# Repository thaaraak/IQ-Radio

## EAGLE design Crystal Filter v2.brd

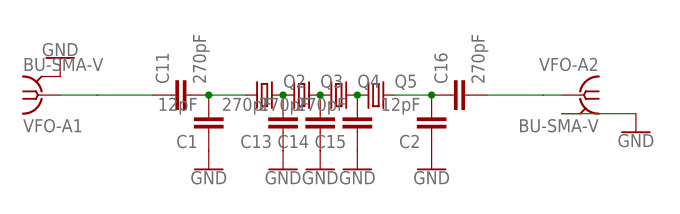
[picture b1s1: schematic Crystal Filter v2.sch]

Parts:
C1, C2: 12pF; C5B3.5
C11, C13, C14, C15, C16: 270pF; C5B3.5
Q2, Q3, Q4, Q5: CRYTALHC49S; HC49/S
VFO-A1, VFO-A2: BU-SMA-V

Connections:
GND: C1.1, C2.1, C13.1, C14.1, C15.1, VFO-A1.2, VFO-A1.3 (2), VFO-A1.4 (2), VFO-A1.5 (2), VFO-A2.2, VFO-A2.3 (2), VFO-A2.4 (2), VFO-A2.5 (2)
unnamed: C1.2, C11.2, Q2.1
unnamed: C16.2, VFO-A2.1
unnamed: C11.1, VFO-A1.1
unnamed: C2.2, C16.1, Q5.2
unnamed: C13.2, Q2.2, Q3.1
unnamed: C14.2, Q3.2, Q4.1
unnamed: C15.2, Q4.2, Q5.1

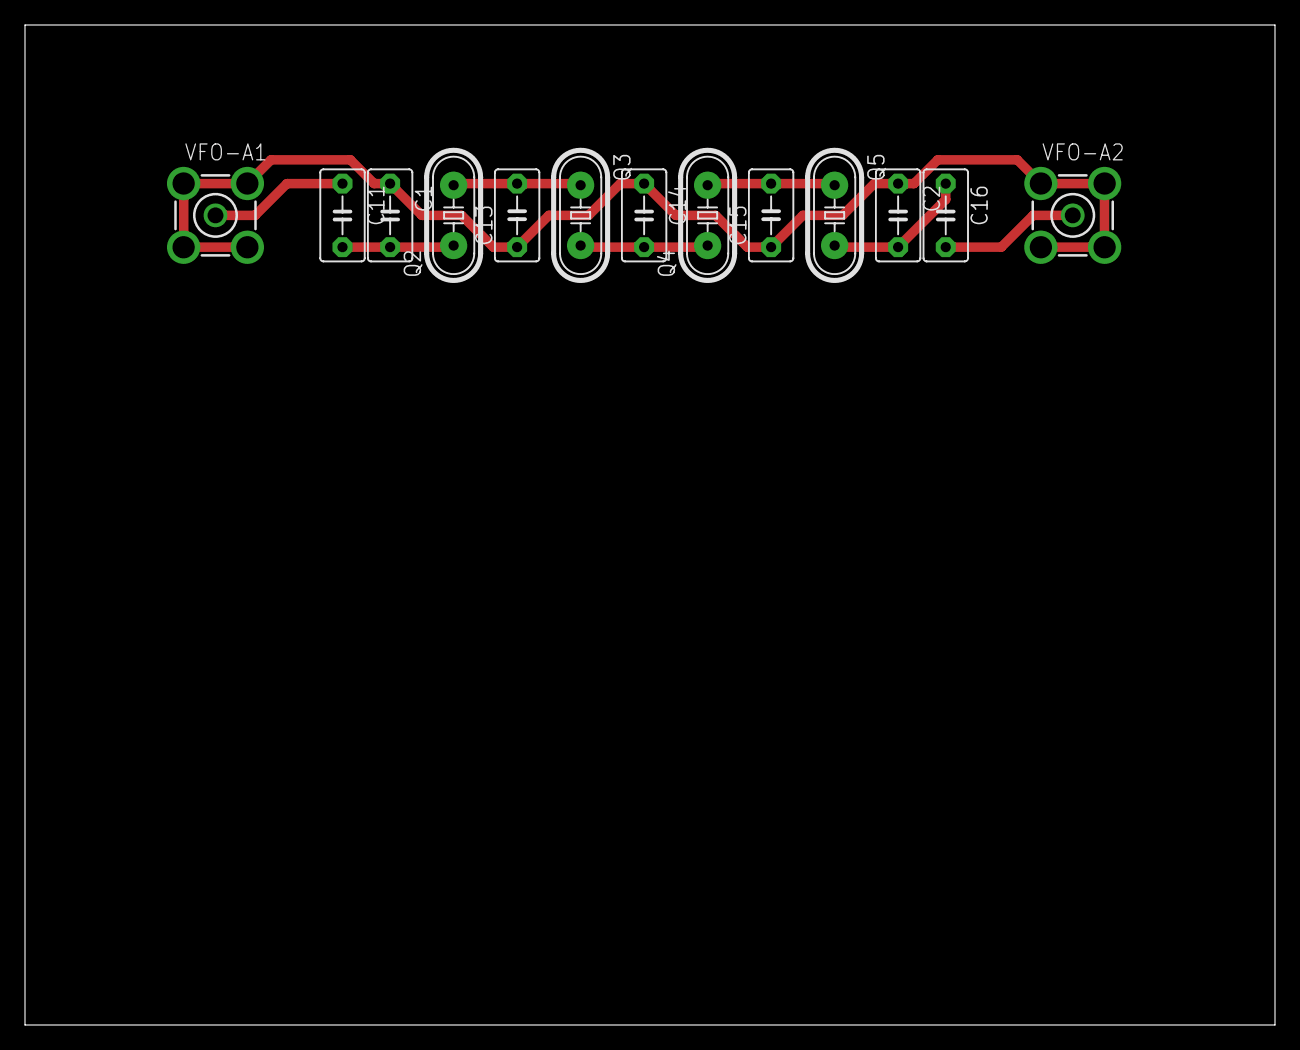
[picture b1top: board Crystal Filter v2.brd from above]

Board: 2 copper layers, 100.0 x 80.0 mm, 13 parts (0 on the bottom side), 8 nets.

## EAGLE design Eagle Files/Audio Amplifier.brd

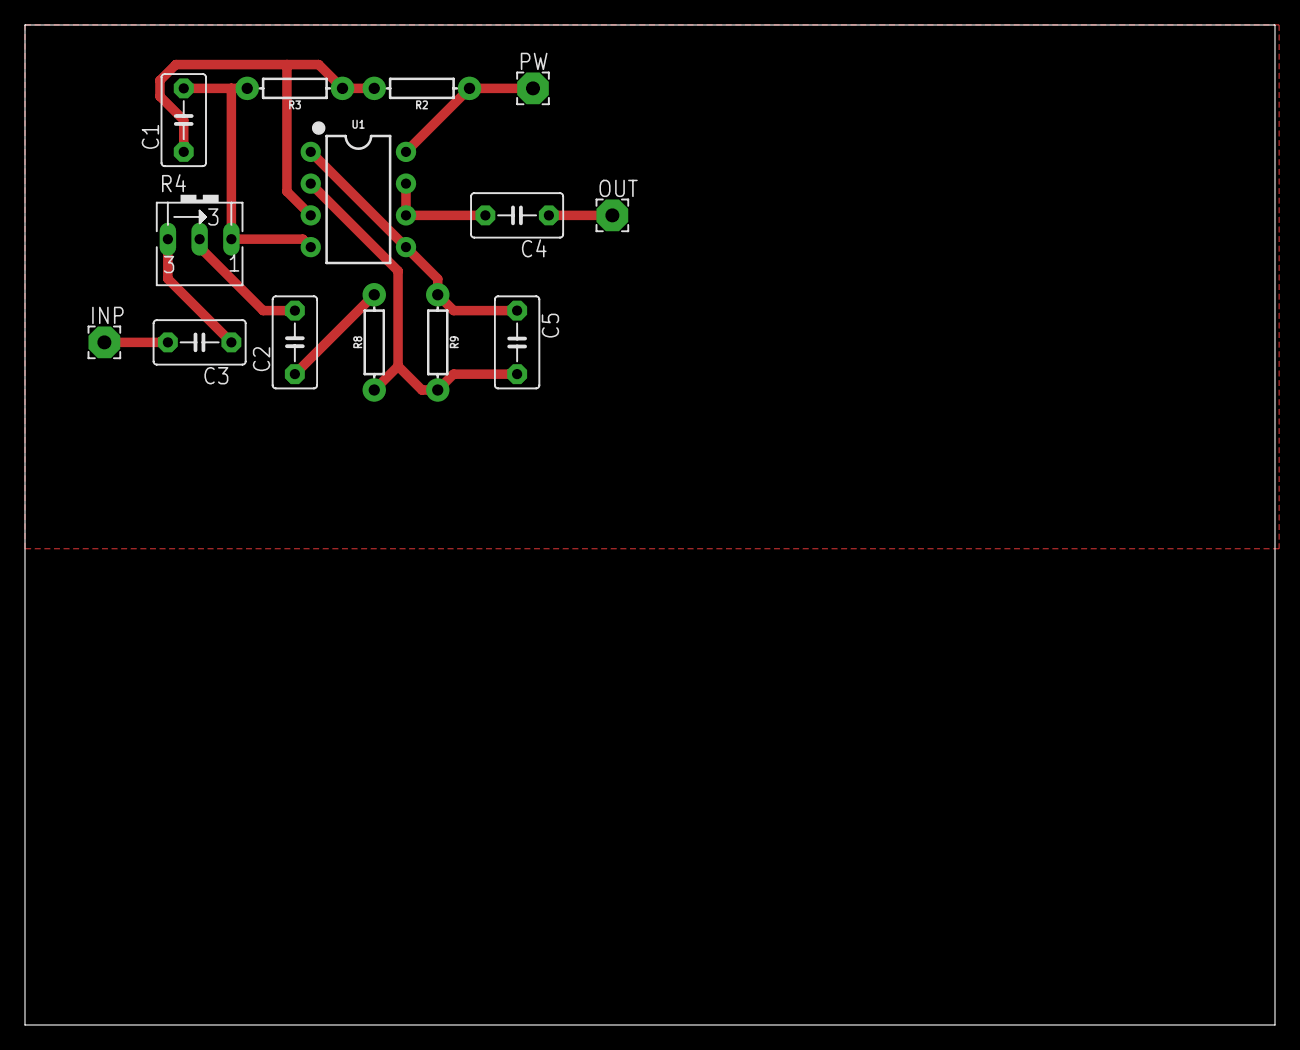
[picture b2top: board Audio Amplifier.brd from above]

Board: 2 copper layers, 100.0 x 80.0 mm, 14 parts (0 on the bottom side), 11 nets.

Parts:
C1, C4: 10uF; C5B3.5
C2, C3: 1uF; C5B3.5
C5: 1nF; C5B3.5
INP: 2,54/1,1
OUT: 2,54/1,1
PW: 2,54/1,1
R2, R3: 10k; AXIAL-0.3
R4: 5k; B25V
R8: 1k; AXIAL-0.3
R9: 120k; AXIAL-0.3
U1: LM358; DIP08

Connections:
GND: C1.2, R3.P$2, R4.A, U1.4
unnamed: C1.1, R2.P$2, R3.P$1, U1.3
unnamed: C2.1, R8.P$2
unnamed: C4.2, U1.6, U1.7
unnamed: C2.2, R4.S
unnamed: C3.1, R4.E
unnamed: C3.2, INP.1
unnamed: C5.2, R8.P$1, R9.P$2, U1.2
unnamed: C4.1, OUT.1
unnamed: C5.1, R9.P$1, U1.1, U1.5
VCC: PW.1, R2.P$1, U1.8

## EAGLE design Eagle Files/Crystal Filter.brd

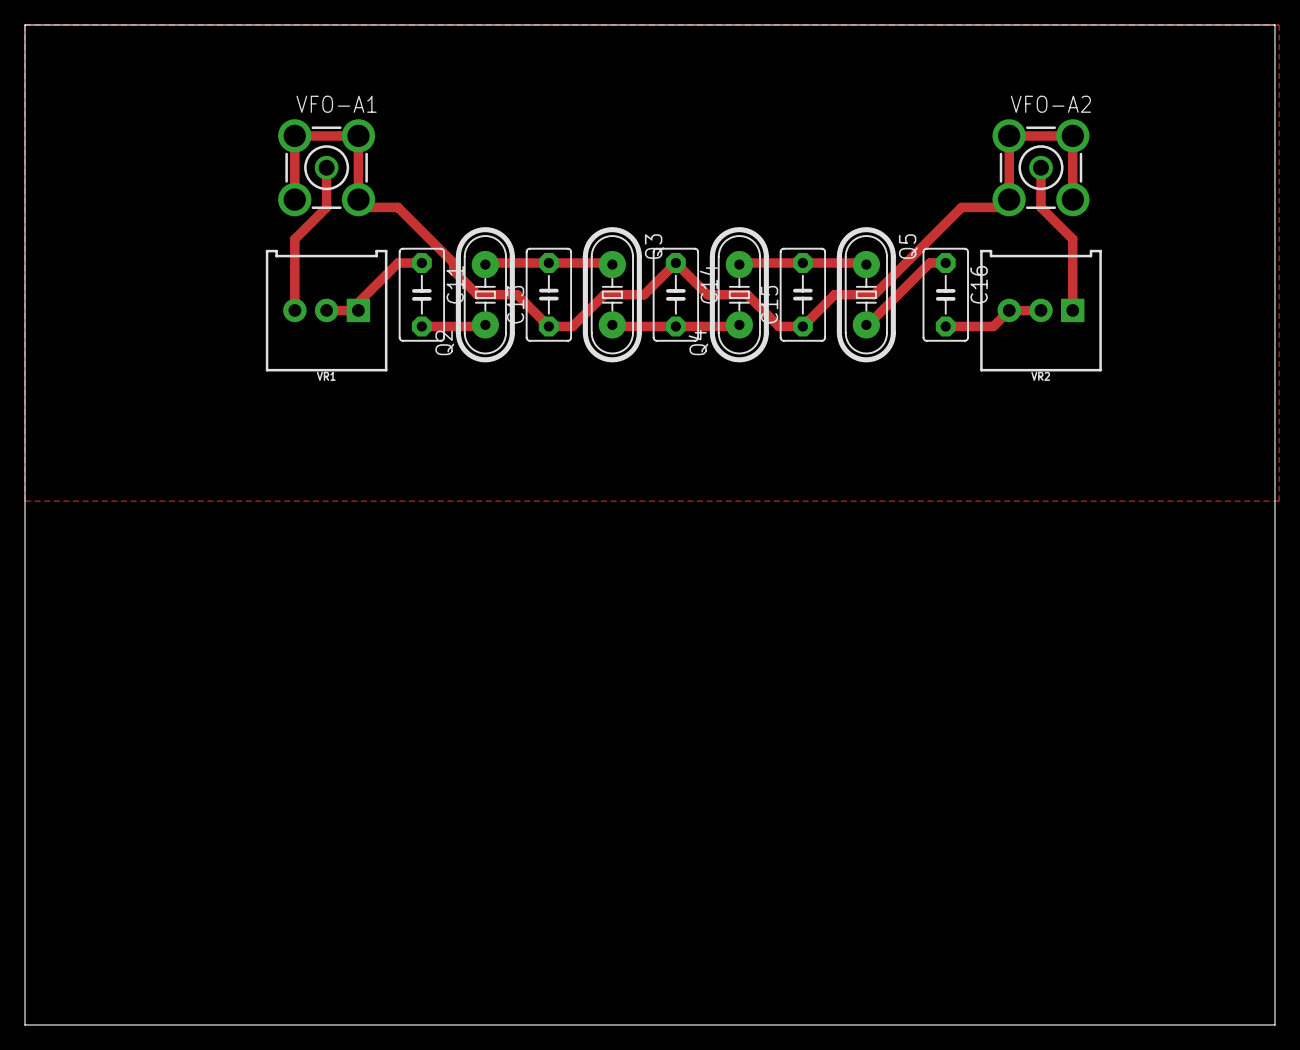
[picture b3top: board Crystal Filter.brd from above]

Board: 2 copper layers, 100.0 x 80.0 mm, 13 parts (0 on the bottom side), 10 nets.

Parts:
C11, C13, C14, C15, C16: 270pF; C5B3.5
Q2, Q3, Q4, Q5: HC49/S
VFO-A1, VFO-A2: BU-SMA-V
VR1, VR2: 500; TRIMPOT-PTH-3386U

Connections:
GND: C13.1, C14.1, C15.1, VFO-A1.2, VFO-A1.3, VFO-A1.4, VFO-A1.5, VFO-A2.2, VFO-A2.3, VFO-A2.4, VFO-A2.5
unnamed: C11.1, VR1.1, VR1.2
unnamed: C16.2, VR2.2, VR2.3
unnamed: VFO-A2.1, VR2.1
unnamed: VFO-A1.1, VR1.3
unnamed: C16.1, Q5.2
unnamed: C11.2, Q2.1
unnamed: C13.2, Q2.2, Q3.1
unnamed: C14.2, Q3.2, Q4.1
unnamed: C15.2, Q4.2, Q5.1

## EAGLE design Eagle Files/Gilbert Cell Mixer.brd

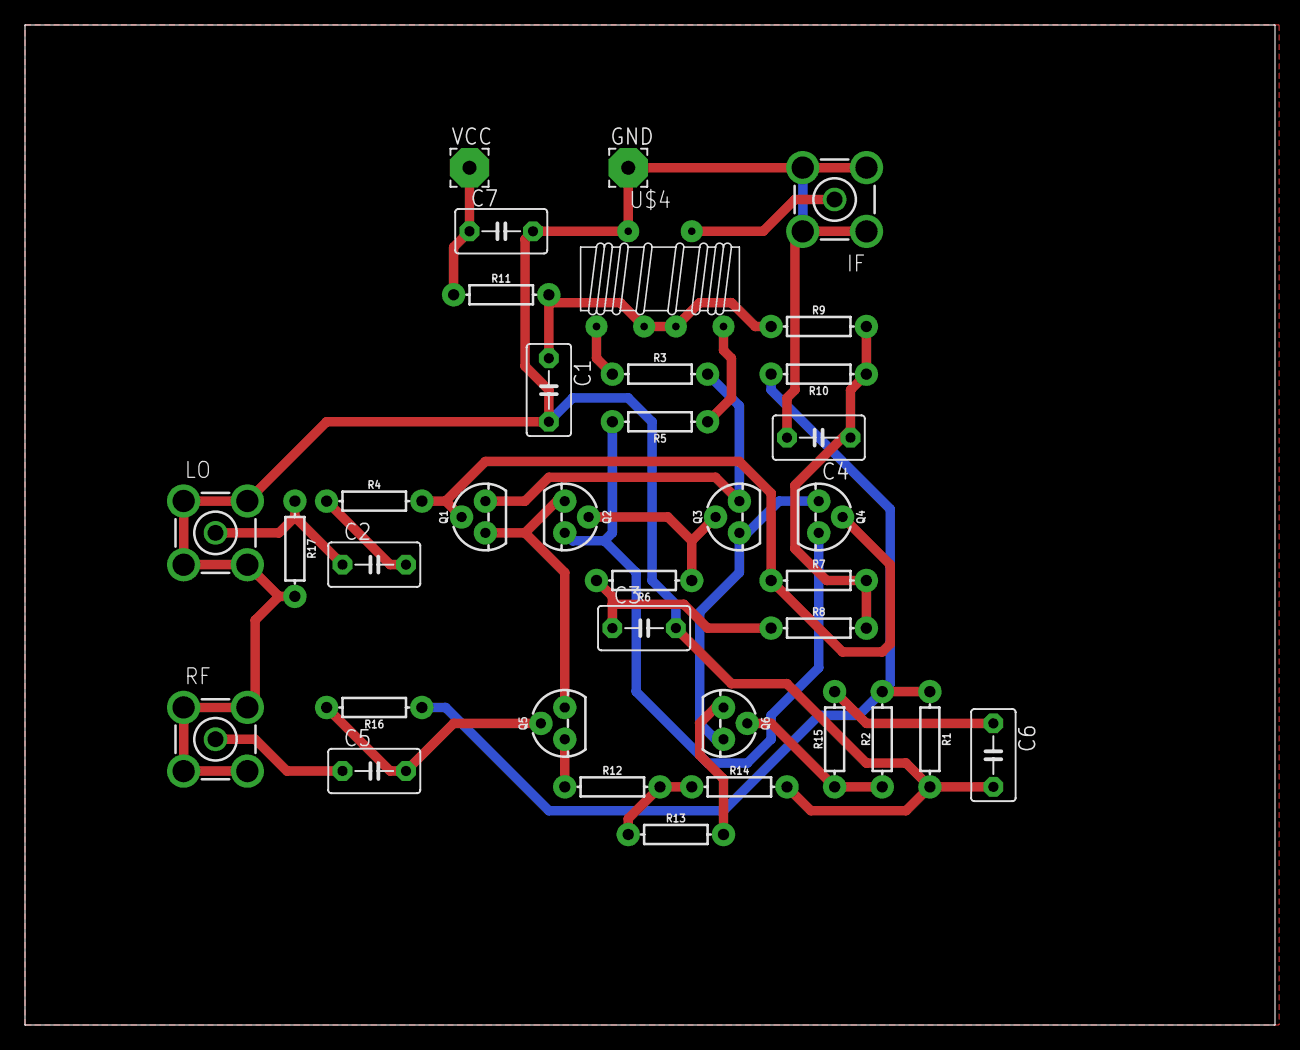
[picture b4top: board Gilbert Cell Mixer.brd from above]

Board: 2 copper layers, 100.0 x 80.0 mm, 36 parts (0 on the bottom side), 24 nets.

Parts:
C1, C2, C3, C4, C5, C6: .1uF; C5B3.5
C7: 100uF; C5B3.5
GND: 3,17/1,1
IF: BU-SMA-V
LO: BU-SMA-V
Q1, Q2, Q3, Q4, Q5, Q6: TO-92
R1: 2k; AXIAL-0.3
R2, R7, R8, R16: 2.2k; AXIAL-0.3
R3, R4, R5, R15: 36; AXIAL-0.3
R6: 10; AXIAL-0.3
R9: 4.7k; AXIAL-0.3
R10: 3k; AXIAL-0.3
R11: 100; AXIAL-0.3
R12, R13: 22; AXIAL-0.3
R14: 300; AXIAL-0.3
R17: 51; AXIAL-0.3
RF: BU-SMA-V
U$4: T50_SPLITTER
VCC: 3,17/1,1

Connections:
GND: C1.2, C3.2, C4.2, C6.2, C7.2, GND.1, IF.2, IF.3, IF.4, IF.5, LO.2, LO.3, LO.4, LO.5, R1.P$2, R14.P$2, R17.P$2, RF.2, RF.3, RF.4, RF.5, U$4.C1A
unnamed: Q1.1, Q2.1, Q5.3
unnamed: Q1.2, Q4.2, R4.P$2, R7.P$1
unnamed: R1.P$1, R2.P$2, R10.P$2, R16.P$1
unnamed: C1.1, R9.P$1, R11.P$2, U$4.C2A, U$4.C3A
unnamed: IF.1, U$4.C1B
unnamed: Q3.1, Q4.1, Q6.3
unnamed: Q1.3, Q3.3, R3.P$2
unnamed: C2.1, LO.1, R17.P$1
unnamed: C3.1, R6.P$2, R8.P$1
unnamed: Q2.3, Q4.3, R5.P$2
unnamed: C6.1, R15.P$2
unnamed: Q6.2, R2.P$1, R15.P$1
unnamed: Q2.2, Q3.2, R6.P$1
unnamed: C4.1, R7.P$2, R8.P$2, R9.P$2, R10.P$1
unnamed: R3.P$1, U$4.C2B
unnamed: R5.P$1, U$4.C3B
unnamed: C2.2, R4.P$1
unnamed: Q5.1, R12.P$1
unnamed: R12.P$2, R13.P$1, R14.P$1
unnamed: Q6.1, R13.P$2
unnamed: C5.1, RF.1
unnamed: C5.2, Q5.2, R16.P$2
VCC: C7.1, R11.P$1, VCC.1

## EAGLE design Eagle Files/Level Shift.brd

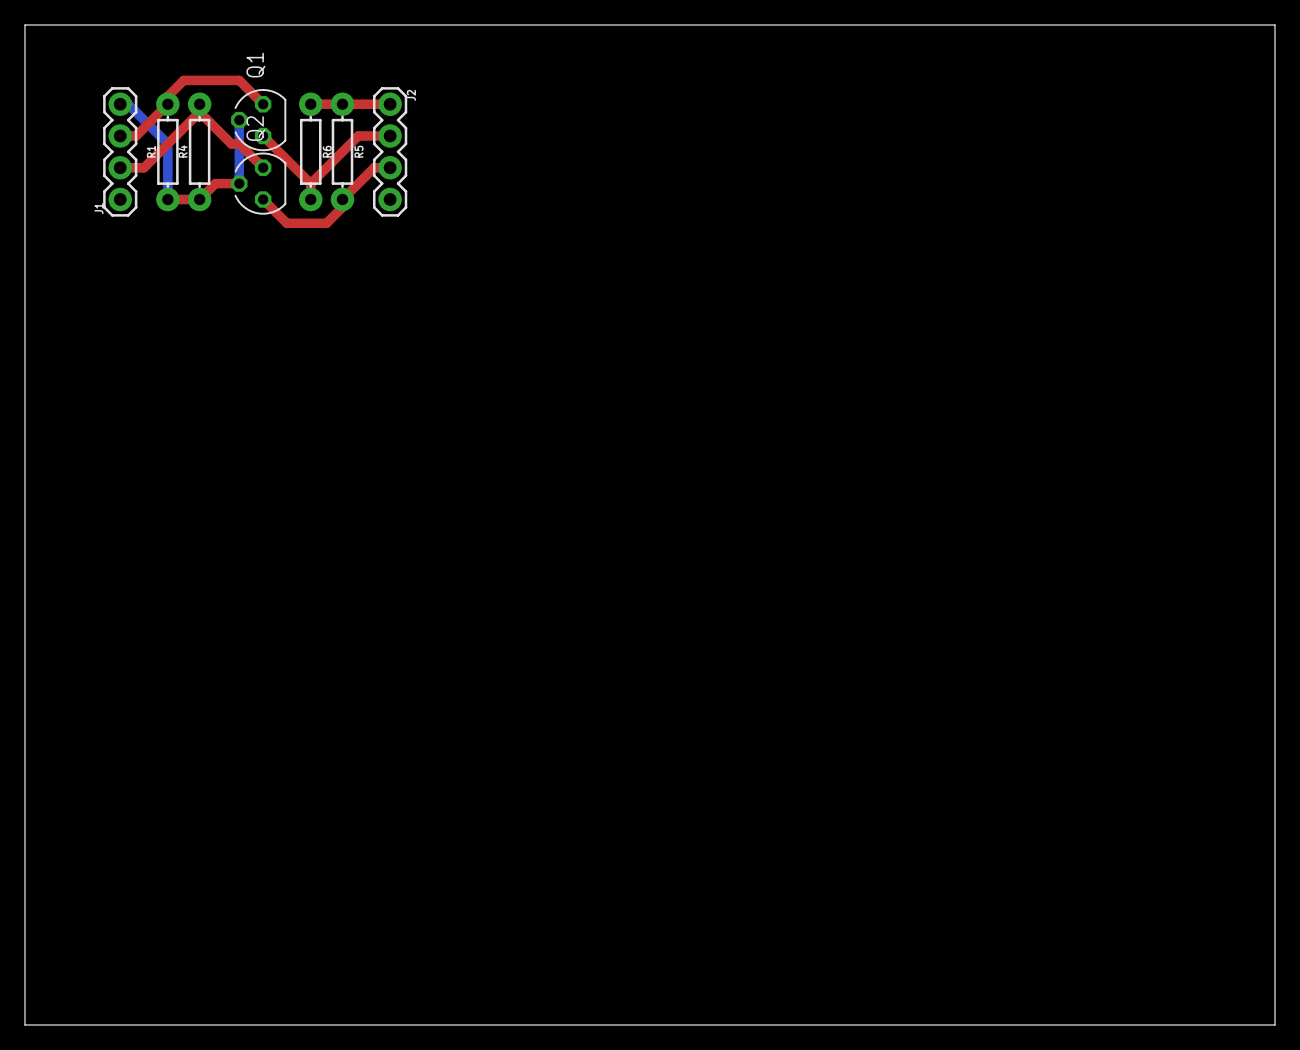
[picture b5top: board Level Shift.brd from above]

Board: 2 copper layers, 100.0 x 80.0 mm, 8 parts (0 on the bottom side), 6 nets.

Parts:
J1, J2: 1X04
Q1, Q2: BS170; SOT54E
R1, R4, R5, R6: 1k; AXIAL-0.3

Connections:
3V: J1.4, Q1.G, Q2.G, R1.P$1, R4.P$1
5V: J2.1, R5.P$1, R6.P$1
unnamed: J1.3, Q1.S, R1.P$2
unnamed: J2.2, Q1.D, R6.P$2
unnamed: J1.2, Q2.S, R4.P$2
unnamed: J2.3, Q2.D, R5.P$2

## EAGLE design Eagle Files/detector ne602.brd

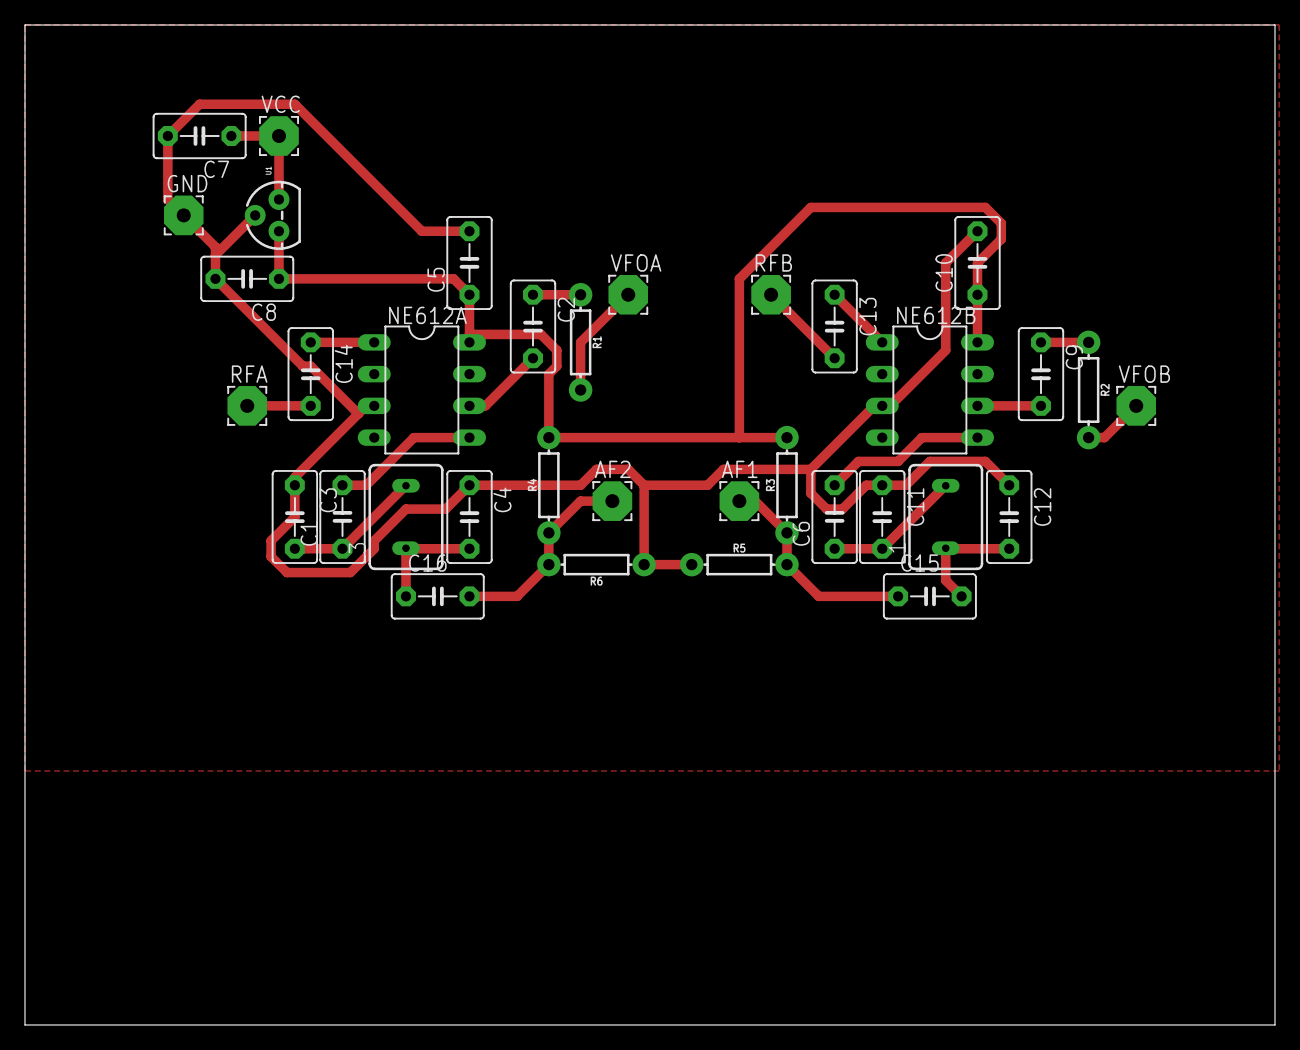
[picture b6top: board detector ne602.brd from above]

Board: 2 copper layers, 100.0 x 80.0 mm, 35 parts (0 on the bottom side), 21 nets.

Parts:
AF1, AF2: 3,17/1,1
C1, C6: 10uF; C5B3.5
C2, C3, C4, C9, C11, C12, C13, C14, C15, C16: 100nF; C5B3.5
C5, C10: .047uF; C5B3.5
C7: 100uF; C5B3.5
C8: 22uf; C5B3.5
GND: 3,17/1,1
L1, L3: 1mH; BS75
NE612A, NE612B: DIL08
R1, R2, R5, R6: 4.7k; AXIAL-0.3
R3, R4: 7.5; AXIAL-0.3
RFA: 3,17/1,1
RFB: 3,17/1,1
U1: TO-92
VCC: 3,17/1,1
VFOA: 3,17/1,1
VFOB: 3,17/1,1

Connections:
8V: C5.1, C8.1, C10.1, NE612A.8, NE612B.8, R3.P$2, R4.P$2, U1.1
GND: C3.1, C4.1, C5.2, C7.2, C8.2, C10.2, C11.1, C12.1, GND.1, NE612A.3, NE612B.3, R5.P$1, R6.P$1, U1.2
unnamed: C1.2, NE612A.5
unnamed: C2.2, NE612A.6
unnamed: C1.1, C3.2, L3.2
unnamed: C4.2, C16.1, L3.1
unnamed: C2.1, R1.P$1
unnamed: R1.P$2, VFOA.1
unnamed: C13.1, NE612B.1
unnamed: C6.2, NE612B.5
unnamed: C9.2, NE612B.6
unnamed: C6.1, C11.2, L1.2
unnamed: C12.2, C15.2, L1.1
unnamed: C9.1, R2.P$1
unnamed: R2.P$2, VFOB.1
unnamed: C14.1, NE612A.1
unnamed: C13.2, RFB.1
unnamed: C14.2, RFA.1
unnamed: AF1.1, C15.1, R3.P$1, R5.P$2
unnamed: AF2.1, C16.2, R4.P$1, R6.P$2
VCC: C7.1, U1.3, VCC.1

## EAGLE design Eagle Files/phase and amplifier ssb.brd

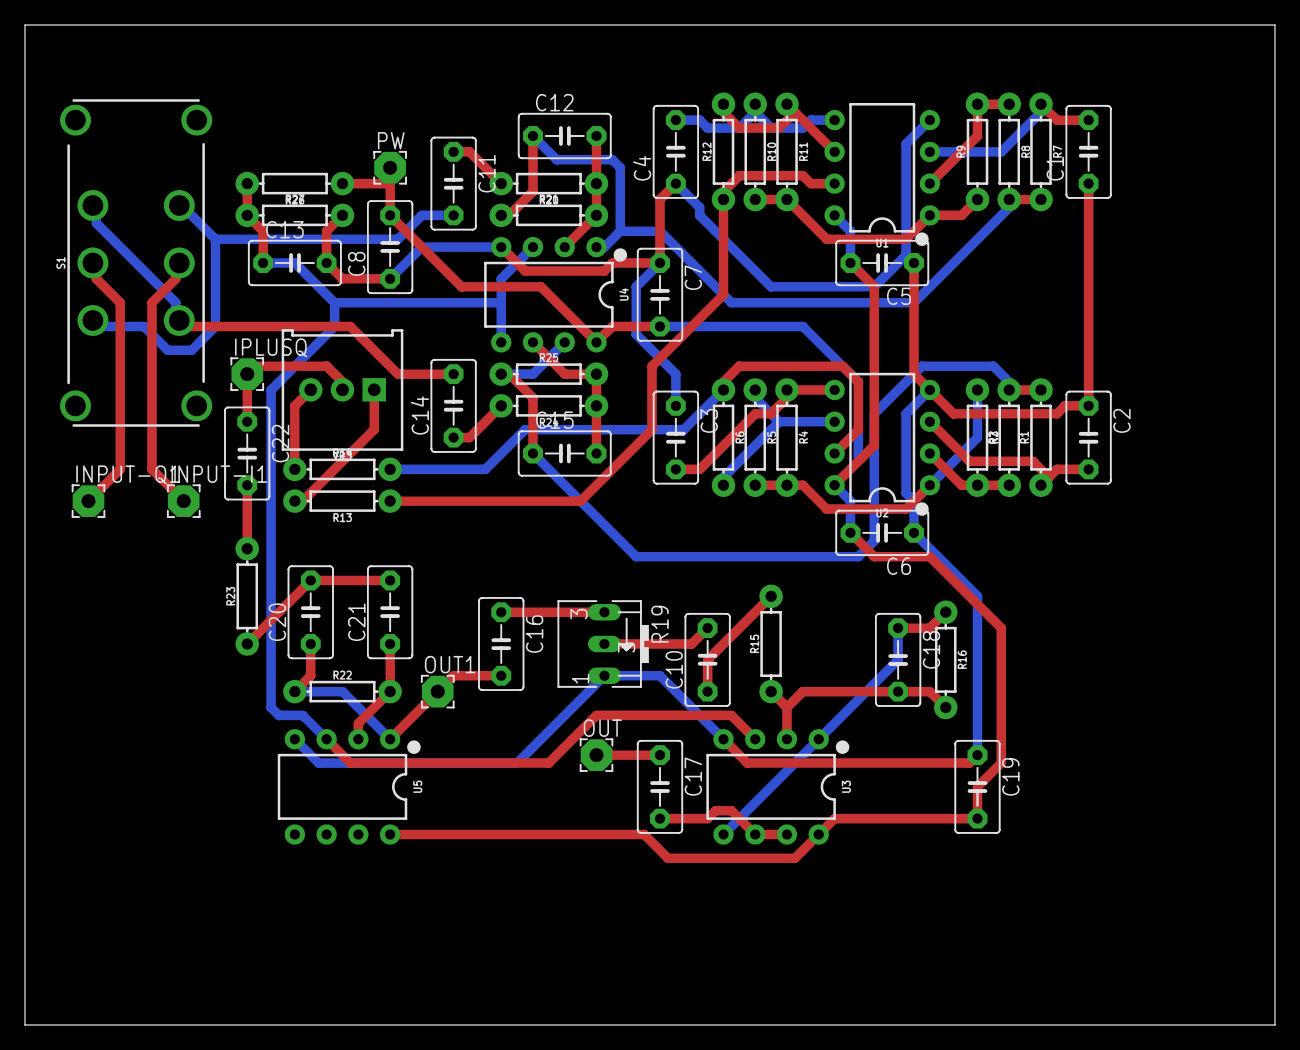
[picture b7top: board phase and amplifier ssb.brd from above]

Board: 2 copper layers, 100.0 x 80.0 mm, 59 parts (0 on the bottom side), 39 nets.

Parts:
C1, C2, C3, C4, C12, C15, C20, C21: 10nF; C5B3.5
C5, C6, C7, C19, C22: 100nF; C5B3.5
C8: 100uF; C5B3.5
C10, C11, C14, C16: 1uF; C5B3.5
C13, C17: 10uF; C5B3.5
C18: 1nF; C5B3.5
INPUT-I1: 2,54/1,1
INPUT-Q1: 2,54/1,1
IPLUSQ: 2,54/1,1
OUT, OUT1: 2,54/1,1
PW: 2,54/1,1
R1: 9.53k; AXIAL-0.3
R2, R3, R5, R6, R8, R9, R11, R12, R23, R26, R27: 10k; AXIAL-0.3
R4: 115k; AXIAL-0.3
R7: 2.32; AXIAL-0.3
R10: 28k; AXIAL-0.3
R13, R14, R15, R20, R24: 1k; AXIAL-0.3
R16: 120k; AXIAL-0.3
R19: 5k; B25V
R21, R25: 100k; AXIAL-0.3
R22: 20k; AXIAL-0.3
S1: SWITCH_DPDT_PTH_GPI-152-3013
U1, U2, U3, U4, U5: LM358; DIP08
VR3: 500; TRIMPOT-PTH-3386U

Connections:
GND: C1.1, C2.1, C3.1, C4.1, C5.1, C6.1, C7.1, C8.1, C13.2, C19.1, R19.A, R27.P$2, U1.4, U2.4, U3.4, U4.4, U5.4
unnamed: C2.2, R1.P$1, U2.3
unnamed: R2.P$1, R3.P$2, U2.2
unnamed: R3.P$1, R4.P$2, R5.P$2, U2.1
unnamed: C13.1, R26.P$2, R27.P$1, U3.3, U4.3, U4.5, U5.3
unnamed: C3.2, R4.P$1, U2.5
unnamed: R5.P$1, R6.P$2, U2.6
unnamed: R8.P$1, R9.P$2, U1.2
unnamed: R6.P$1, R14.P$2, U2.7
unnamed: C1.2, R7.P$1, U1.3
unnamed: C12.1, R7.P$2, R8.P$2, R21.P$1, U4.1
unnamed: C4.2, R10.P$1, U1.5
unnamed: R9.P$1, R10.P$2, R11.P$2, U1.1
unnamed: R11.P$1, R12.P$2, U1.6
unnamed: R13.P$2, VR3.1
unnamed: R12.P$1, R13.P$1, U1.7
unnamed: R14.P$1, VR3.3
unnamed: C22.1, IPLUSQ.1, VR3.2
unnamed: C15.1, R1.P$2, R2.P$2, R25.P$1, U4.7
unnamed: C11.2, S1.10, S1.21
unnamed: C18.1, R16.P$1, U3.1, U3.5
unnamed: C18.2, R15.P$1, R16.P$2, U3.2
unnamed: INPUT-I1.1, S1.C@1
unnamed: C10.1, R15.P$2
unnamed: C10.2, R19.S
unnamed: C16.1, R19.E
unnamed: C17.2, U3.6, U3.7
unnamed: C12.2, R20.P$1, R21.P$2, U4.2
unnamed: C14.2, S1.11, S1.20
unnamed: C11.1, R20.P$2
unnamed: C17.1, OUT.1
unnamed: C15.2, R24.P$1, R25.P$2, U4.6
unnamed: C22.2, R23.P$2
unnamed: C14.1, R24.P$2
unnamed: C16.2, C20.1, OUT1.1, R22.P$1, U5.1
unnamed: C21.1, R22.P$2, U5.2
unnamed: C20.2, C21.2, R23.P$1
unnamed: INPUT-Q1.1, S1.C@2
VCC: C5.2, C6.2, C7.2, C8.2, C19.2, PW.1, R26.P$1, U1.8, U2.8, U3.8, U4.8, U5.8

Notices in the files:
parts and their libraries:
SparkFun-PowerSymbols: Licensing: Creative Commons ShareAlike 4.0 International - https://creativecommons.org/licenses/by-sa/4.0
